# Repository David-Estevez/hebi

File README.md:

hebi
====

Electronics board for modular robots

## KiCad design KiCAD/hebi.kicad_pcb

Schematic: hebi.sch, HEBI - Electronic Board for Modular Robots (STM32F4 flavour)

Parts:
C5, C11, C12, C16, C17, C19, C20, C22, C23, C24, C26, C27: 100nF
C6, C7: 24pF
C9, C10, C28, C29: 1uF
C13: 4.7uF X7R 0805
C15: 1uF X7R 0805
C18, C21: 2.2uF
C25: 22uF
CR1, CR2: CG0603MLC-05LE
D1: GREEN
D2: ORANGE
D3: RED
D4: BLUE
D5, D6: D_SCHOTTKY
F1: MF-MSMF050-2
JP2: JP_5
JP3, JP4, JP5, JP6: JUMPER-2
K1, K2, K3, K4, K5: CONN_3
L1: fcm 0603
P1, P2, P3, P4: CONN_4
P6: CONN_2
Q1, Q2, Q3, Q4, Q5, Q6, Q7, Q9, Q10: MOS_N_DIODE
R1: 100K
R2: 220K
R3: 47
R5, R10, R11: 510
R6, R7, R8: 680
R12, R13: 22R
R14: 4.7K
R15, R16, R17, R18, R19, R20, R21, R22, R23, R24, R25, R26, R27, R28, R31, R32, R33, R34: 10K
SW1, SW2, SW3: SW_PUSH
U3: MCP1825S
U4: STM32F407VG; TQFP100
U5: XBEE
USB1: USBCONN
X1: 8MHz

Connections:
+5V: C13.1, D5.1, D6.1, R20.1, R21.1, R22.1, R23.1, R24.1, R27.1, R28.1, R33.1, R34.1, U3.1 (Vin)
/ADC1: K1.1, U4.15 (PC0/OTG_HS_ULPI_STP/EVENTOUT)
/ADC2: K1.2 (PM), U4.16 (PC1/ETH_MDC/_EVENTOUT)
/ADC3: K1.3, U4.33 (PC4/ETH_RMII_RX_D0/ETH_MII_RX_D0/EVENTO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)
/BOOT0: R11.1, SW3.2, U4.94 (BOOT0)
/BOOT1: R10.1, U4.37 (PB2/BOOT1/EVENTOUT)
/D+: R12.1, U4.71 (PA12/USART1_RTS/CAN1_TX/TIM1_ETR/OTG_FS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)
/D-: R13.1, U4.70 (PA11/USART1_CTS/CAN1_RX/TIM1_CH4_/OTG_F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)
/I2C_SCL_PWR_3V: Q2.S, R16.2, U4.67 (PA8/MCO1/USART1_CK/TIM1_CH1/I2C3_SCL/OT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)
/I2C_SCL_PWR_5V: P6.2 (PM), Q2.D, R21.2
/I2C_SDA_PWR_3V: Q1.S, R15.2, U4.66 (PC9/I2S_CKIN/MCO2/TIM8_CH4/SDIO_D1/I2C3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)
/I2C_SDA_PWR_5V: P6.1, Q1.D, R20.2
/LED1: D1.1 (A), U4.4 (PE5/TRACED2/FSMC_A21/TIM9_CH1/DCMI_D6/E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)
/LED2: D2.1 (A), U4.95 (PB8/TIM4_CH3/SDIO_D4/TIM10_CH1/DCMI_D6/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)
/LED3: D3.1 (A), U4.96 (PB9/SPI2_NSS/I2S2_WS/TIM4_CH4/TIM11_CH1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)
/LED4: D4.1 (A), U4.53 (PB14/SPI2_MISO/TIM1_CH2N/TIM12_CH1/OTG_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)
/PUSH_SW: R2.1, SW2.2, U4.59 (PD12/FSMC_ALE/FSMC_A17/TIM4_CH1/USART3_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)
/RESET: C5.1, JP2.4, R1.2, SW1.1, U4.14 (NRST)
/RX1: P1.2, U4.87 (PD6/FSMC_NWAIT/USART2_RX/EVENTOUT)
/RX2: P3.2, U4.64 (PC7/I2S3_MCK/TIM8_CH2/SDIO_D7/USART6_RX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)
/RX3: P2.2, U4.56 (PD9/FSMC_D14/USART3_RX/EVENTOUT)
/RX4: P4.2, U4.93 (PB7/I2C1_SDA/FSMC_NL/DCMI_VSYNC/USART1_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)
/SERVO1_3V: Q3.S, R17.2, U4.40 (PE9/FSMC_D6/TIM1_CH1/EVENTOUT)
/SERVO1_5V: K3.3, Q3.D, R22.2
/SERVO2_3V: Q4.S, R18.2, U4.65 (PC8/TIM8_CH3/SDIO_D0/TIM3_CH3/USART6_CK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)
/SERVO2_5V: K4.3, Q4.D, R23.2
/SERVO3_3V: Q5.S, R19.2, U4.35 (PB0/TIM3_CH3/TIM8_CH2N/OTG_HS_ULPI_D1/E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)
/SERVO3_5V: K5.3, Q5.D, R24.2
/SERVO_PWR: C29.1, K2.2 (PM), K3.2 (PM), K4.2 (PM), K5.2 (PM)
/SPI1_MISO: U4.31 (PA6/SPI1_MISO/TIM8_BKIN/TIM13_CH1/DCMI_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)
/SPI1_MOSI: U4.32 (PA7/SPI1_MOSI/TIM8_CH1N/TIM14_CH1/TIM3_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)
/SPI1_NSS: U4.29 (PA4/SPI1_NSS/SPI3_NSS/USART2_CK/DCMI_HS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)
/SPI1_SCK: U4.30 (PA5/SPI1_SCK/OTG_HS_ULPI_CK/TIM2_CH1_ET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)
/SWCLK: JP2.3, U4.76 (PA14/JTCK/SWCLK/EVENTOUT)
/SWDIO: JP2.2, U4.72 (PA13/JTMS/SWDIO/EVENTOUT)
/TX1: JP3.2, P1.3, Q6.D, R27.2
/TX1_3V: JP3.1, Q6.S, R25.2, U4.86 (PD5/FSMC_NWE/USART2_TX/EVENTOUT)
/TX2: JP5.2, P3.3, Q9.D, R33.2
/TX2_3V: JP5.1, Q9.S, R31.2, U4.63 (PC6/I2S2_MCK/TIM8_CH1/SDIO_D6/USART6_TX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)
/TX3: JP4.2, P2.3, Q7.D, R28.2
/TX3_3V: JP4.1, Q7.S, R26.2, U4.55 (PD8/FSMC_D13/USART3_TX/EVENTOUT)
/TX4: JP6.2, P4.3, Q10.D, R34.2
/TX4_3V: JP6.1, Q10.S, R32.2, U4.92 (PB6/I2C1_SCL/TIM4_CH1/CAN2_TX/DCMI_D5/U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)
/T_SWO: U4.89 (PB3/JTDO/TRACESWO/SPI3_SCK/I2S3_CK/TIM2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)
/VBUS: C25.1, F1.1 (A), USB1.1 (VBUS)
/VIN: D5.2, K2.1
/VUSB: C22.1, D6.2, F1.2 (B)
/XBEE_RESET: R14.2, U5.5 (RESET)
/XBEE_RX: U4.23 (PA0/WKUP/USART2_CTS/UART4_TX/ETH_MII_CR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), U5.3 (DIN)
/XBEE_SLEEP: U4.97 (PE0/TIM4_ETR/FSMC_NBL0/DCMI_D2/EVENTOUT), U5.9 (^DTR/DI8)
/XBEE_TX: U4.24 (PA1/USART2_RTS/UART4_RX/ETH_RMII_REF_CL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), U5.2 (DOUT)
GND: C5.2, C6.1, C7.1, C9.2, C10.2, C11.2, C12.2, C13.2, C15.2, C16.1, C17.1, C18.2, C19.1, C20.1, C21.2, C22.2, C23.1, C24.1, C25.2, C26.1, C27.1, C28.1, C29.2, CR1.2 (Anode), CR2.2 (Anode), JP2.5, K2.3, K3.1, K4.1, K5.1, P1.4, P2.4, P3.4, P4.4, R2.2, R5.2, R6.2, R7.2, R8.2, R10.2, R11.2, SW1.2, U3.2 (GND), U3.4 (GND), U4.10 (VSS), U4.20 (VSSA), U4.27 (VSS), U4.74 (VSS), U4.99 (VSS), U5.10 (GND), USB1.4 (GND), USB1.5 (SHIELD)
unnamed: C9.1, C11.1, L1.2, R3.1, U4.22 (VDDA)
unnamed: C10.1, C12.1, R3.2, U4.21 (VREF+)
unnamed: C21.1, U4.73 (VCAP_2)
unnamed: C18.1, U4.49 (VCAP_1)
unnamed: CR1.1 (cathode), R12.2, USB1.3 (DP)
unnamed: CR2.1 (cathode), R13.2, USB1.2 (DN)
unnamed: D4.2 (K), R8.1
unnamed: D3.2 (K), R7.1
unnamed: D2.2 (K), R6.1
unnamed: D1.2 (K), R5.1
unnamed: C6.2, U4.12 (PH0/OSC_IN/EVENTOUT), X1.1
unnamed: C7.2, U4.13 (PH1/OSC_OUT/EVENTOUT), X1.2
VCC: C15.1, C16.2, C17.2, C19.2, C20.2, C23.2, C24.2, C26.2, C27.2, C28.2, JP2.1, L1.1, P1.1, P2.1, P3.1, P4.1, Q1.G, Q2.G, Q3.G, Q4.G, Q5.G, Q6.G, Q7.G, Q9.G, Q10.G, R1.1, R14.1, R15.1, R16.1, R17.1, R18.1, R19.1, R25.1, R26.1, R31.1, R32.1, SW2.1, SW3.1, U3.3 (Vout), U4.6 (VBAT), U4.11 (VDD), U4.19 (VDD), U4.28 (VDD), U4.50 (VDD), U4.75 (VDD), U4.100 (VDD), U5.1 (VCC)

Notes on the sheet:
NOTE: VBAT is the RTC backup power supply, and must lie between 1.65V and 3.6V
Power supply filtering
USER button
RESET button
BOOT configuration (for enabling the bootloader)
Analog power supply
It might be useful to make VSSA to go to a analog ground plane
SWD (Serial wire debugging) connector
USB Port
or-ing power supplies circuit
LED indicators
SERVO headers
Serial ports to other modules
xBee connector
Connector for the power suppy module
LDO Power Regulator In: 5-6V Out: 3V
'0' > from flash '1' > DFU Mode
ADC connector
Power Flags
STM32F4 Microcontroller
Since this needs 9.6V to work I'm currently thinking of breaking out the 3 control pins ( Rx, Tx, Dir) to connect them to an expansion module.
DYNAMIXEL servo control

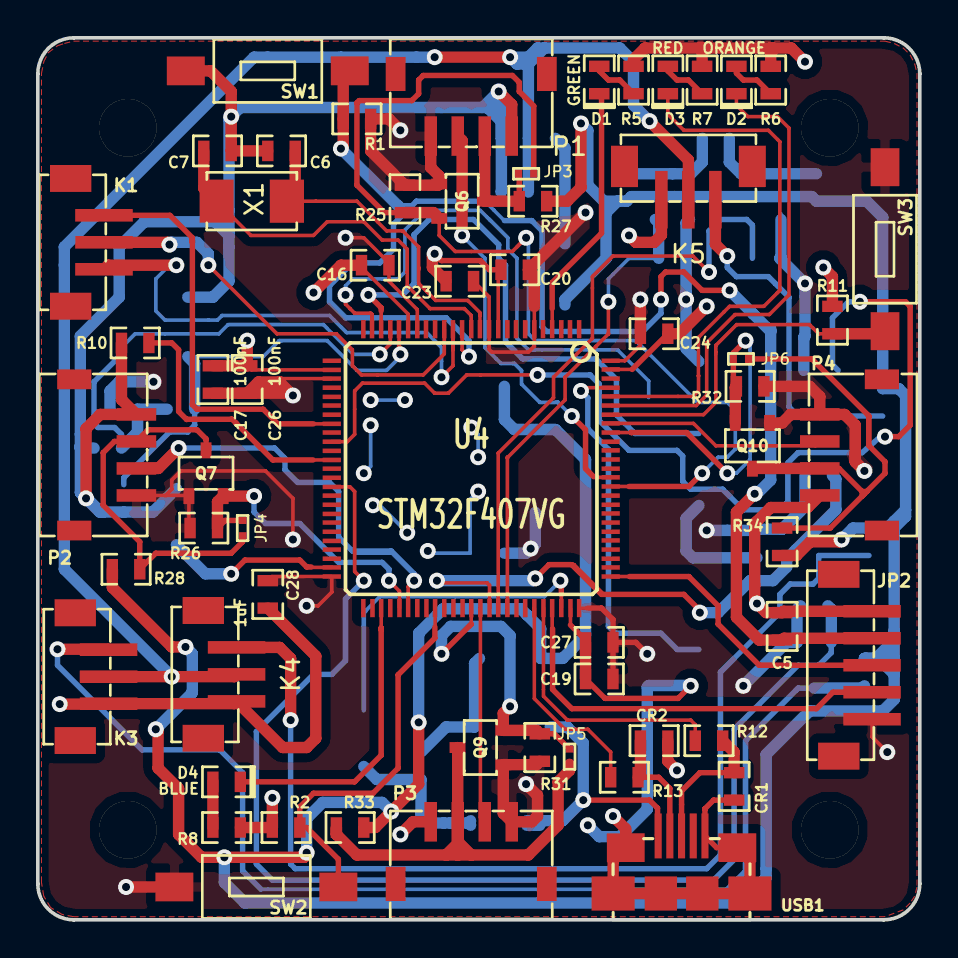
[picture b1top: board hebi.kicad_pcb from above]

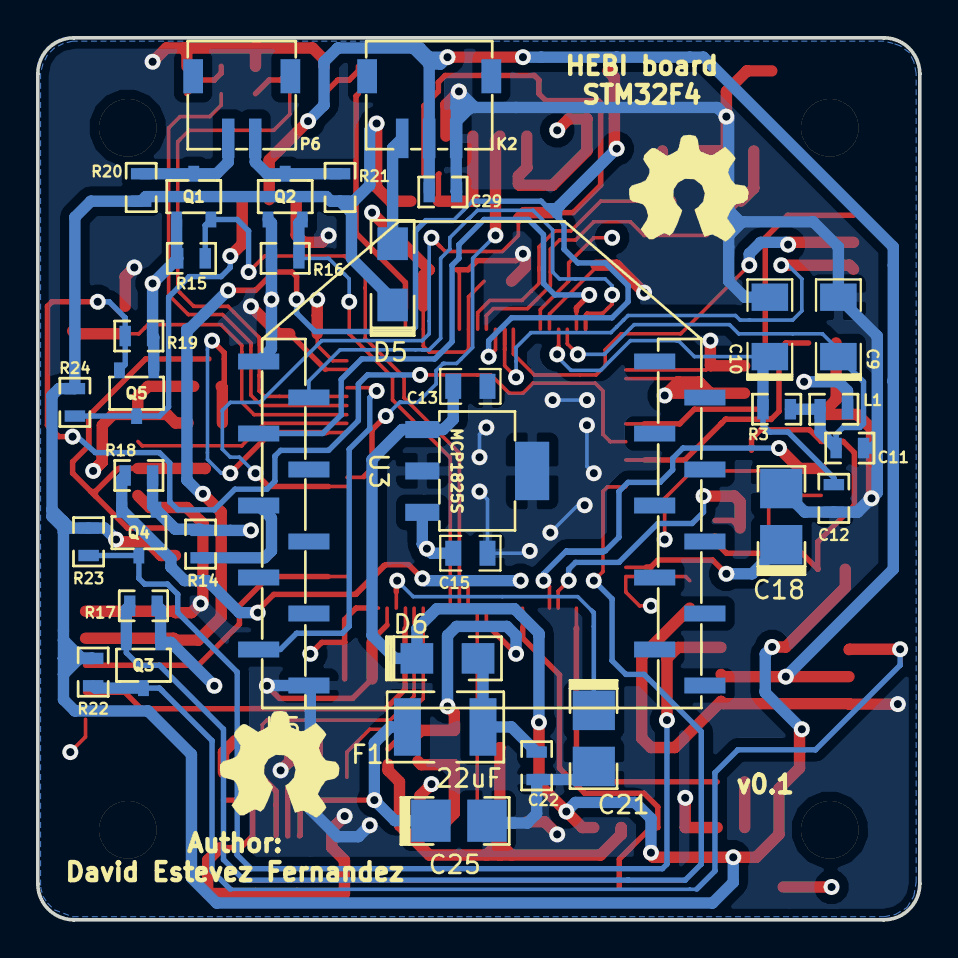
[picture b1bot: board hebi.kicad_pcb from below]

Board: 4 copper layers, 49.0 x 49.0 mm, 99 parts (36 on the bottom side), 60 nets.

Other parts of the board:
Taladro3mm, Taladro3mm#2, Taladro3mm#3, Taladro3mm#4: 3mm; Taladro3mm

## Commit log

2013-08-08 Basic design. Just basic circuitry for uC
2013-08-08 Added connectors for some peripherals.
2013-08-09 Perfboard prototype
2013-08-09 Small changes.
2013-08-15 Prototype design updated.
2013-08-27 Added Arduino test01 for testing board.
2013-08-28 Schematic updated.
2013-08-29 Test 1 updated to test also servos
2014-01-15 Added MCU and basic circuits. Pin assignment.
2014-01-16 Added Power supply filtering and usb port
2014-01-17 Added serial ports and servo connectors.
2014-01-21 Added buffers for serial ports, dynamixel connector.
2014-01-22 Corrected xbee pinout, corrected serial buffers.
2014-01-27 Added IMU.
2014-01-27 Added power regulator.
2014-01-27 Added libraries for new components.
2014-01-28 Added component values.
2014-01-30 Added ADC connector.
2014-01-30 Finished most of the schematic (except power selection).
2014-01-31 Added or-ing circuit
2014-01-31 ERC checked. Generated Netlist.
2014-02-07 Modified some schematic values.
2014-02-07 Added bom file.
2014-02-10 Assigned some footprints to netlist.
2014-02-11 More footprints added.
2014-02-13 Changed Opendous to Opendous Custom. Added Footprints for ZH connectors.
2014-02-14 Added last two ZH connectors.
2014-02-17 Added XBee footprint.
2014-02-18 Added new magnetic compass.
2014-02-19 Solved IMU issue on schematic, changed annotation.
2014-02-20 Created new footprints for the MPU-6050 and HMC58583L.
2014-02-24 Added footprints.
2014-02-24 Added regulator footprint.
2014-02-24 Placed footprints on pcb view.
2014-03-21 Placed some components on the PCB.
2014-03-24 Placed more footprints on board.
2014-03-24 Removed dynamixel due to spatial requirements (no space left for that)
2014-03-25 Routed front layer (mostly, without vias)
2014-03-27 Traced more traces.
2014-03-28 Added even more tracks.
2014-04-01 Routed even more things.
2014-04-02 Routed power tracks, removed IMU.
2014-04-09 Routed things, power planes added, rounded corners.
2014-04-10 Fixed silkscreen (now it is nice)
2014-04-21 Modified electrolytic capacitor to tantalum one.
2014-09-03 Minor fixes.
